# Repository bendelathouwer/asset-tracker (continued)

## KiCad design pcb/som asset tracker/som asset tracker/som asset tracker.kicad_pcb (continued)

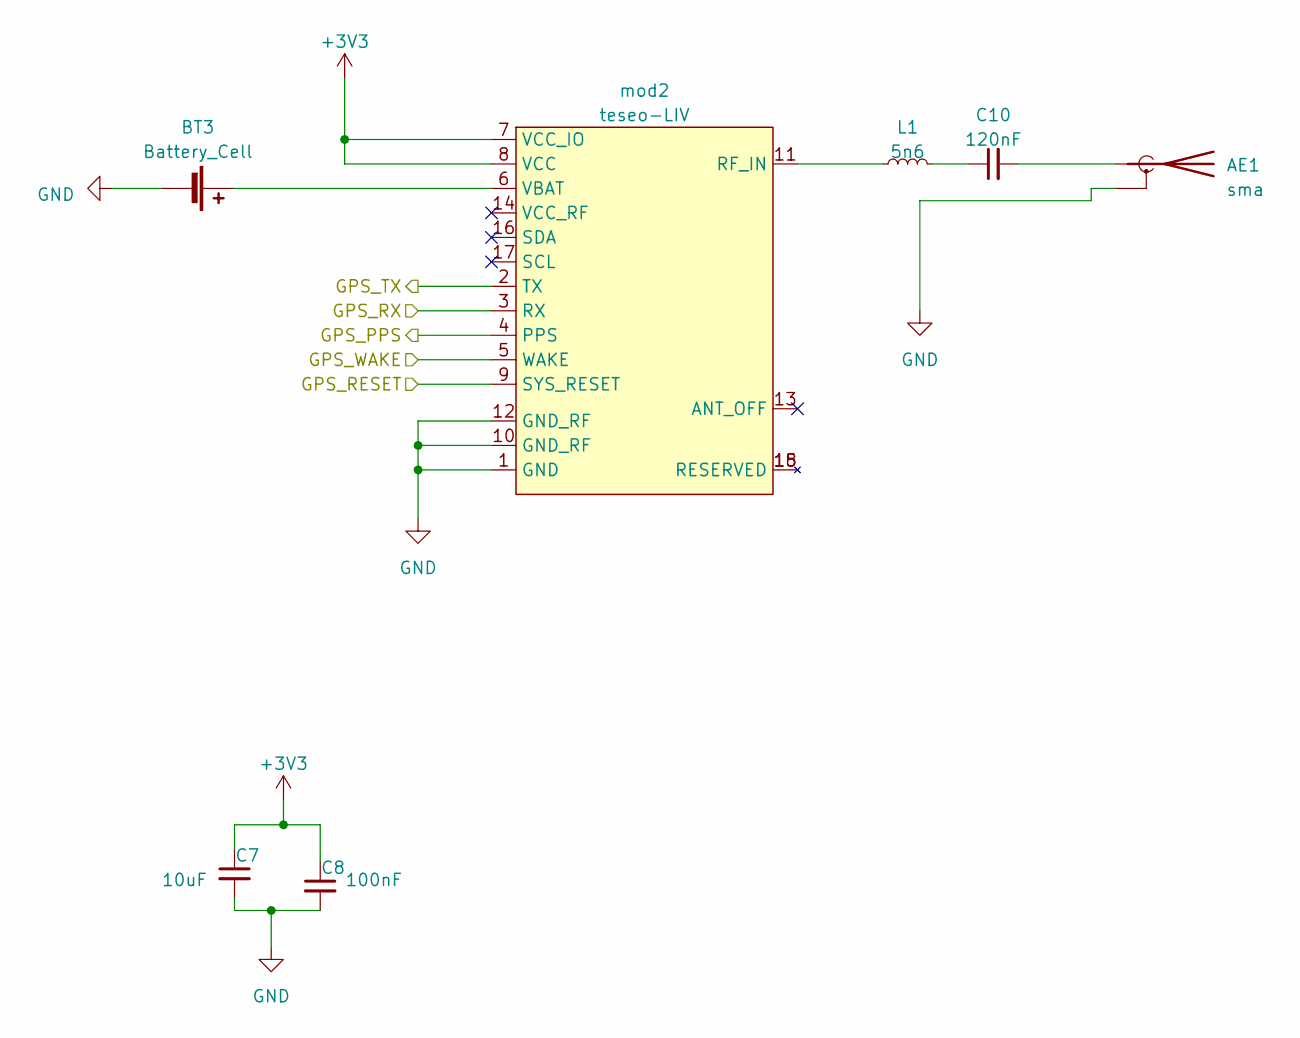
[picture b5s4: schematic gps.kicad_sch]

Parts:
AE1: sma; sma_right angeld
BT3: Battery_Cell; 3012TR
C7: 10uF; 0603
C8: 100nF; 0603
C10: 120nF; 0603
L1: 5n6; 0603
mod2: teseo-LIV; SON_STM_TESEO-LIV3R

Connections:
+3V3: C7.1, C8.1, mod2.7 (VCC_IO), mod2.8 (VCC); also elsewhere on the board
/PPS: mod2.4 (PPS); also elsewhere on the board
/RESET: mod2.9 (SYS_RESET); also elsewhere on the board
/RX: mod2.3 (RX); also elsewhere on the board
/TX: mod2.2 (TX); also elsewhere on the board
/WAKE: mod2.5 (WAKE); also elsewhere on the board
GND: AE1.2 (Shield), BT3.2 (-), C7.2, C8.2, mod2.1 (GND), mod2.10 (GND_RF), mod2.12 (GND_RF); also elsewhere on the board
unnamed: AE1.1 (A), C10.2
unnamed: BT3.1 (+), mod2.6 (VBAT)
unnamed: C10.1, L1.2
unnamed: L1.1, mod2.11 (RF_IN)

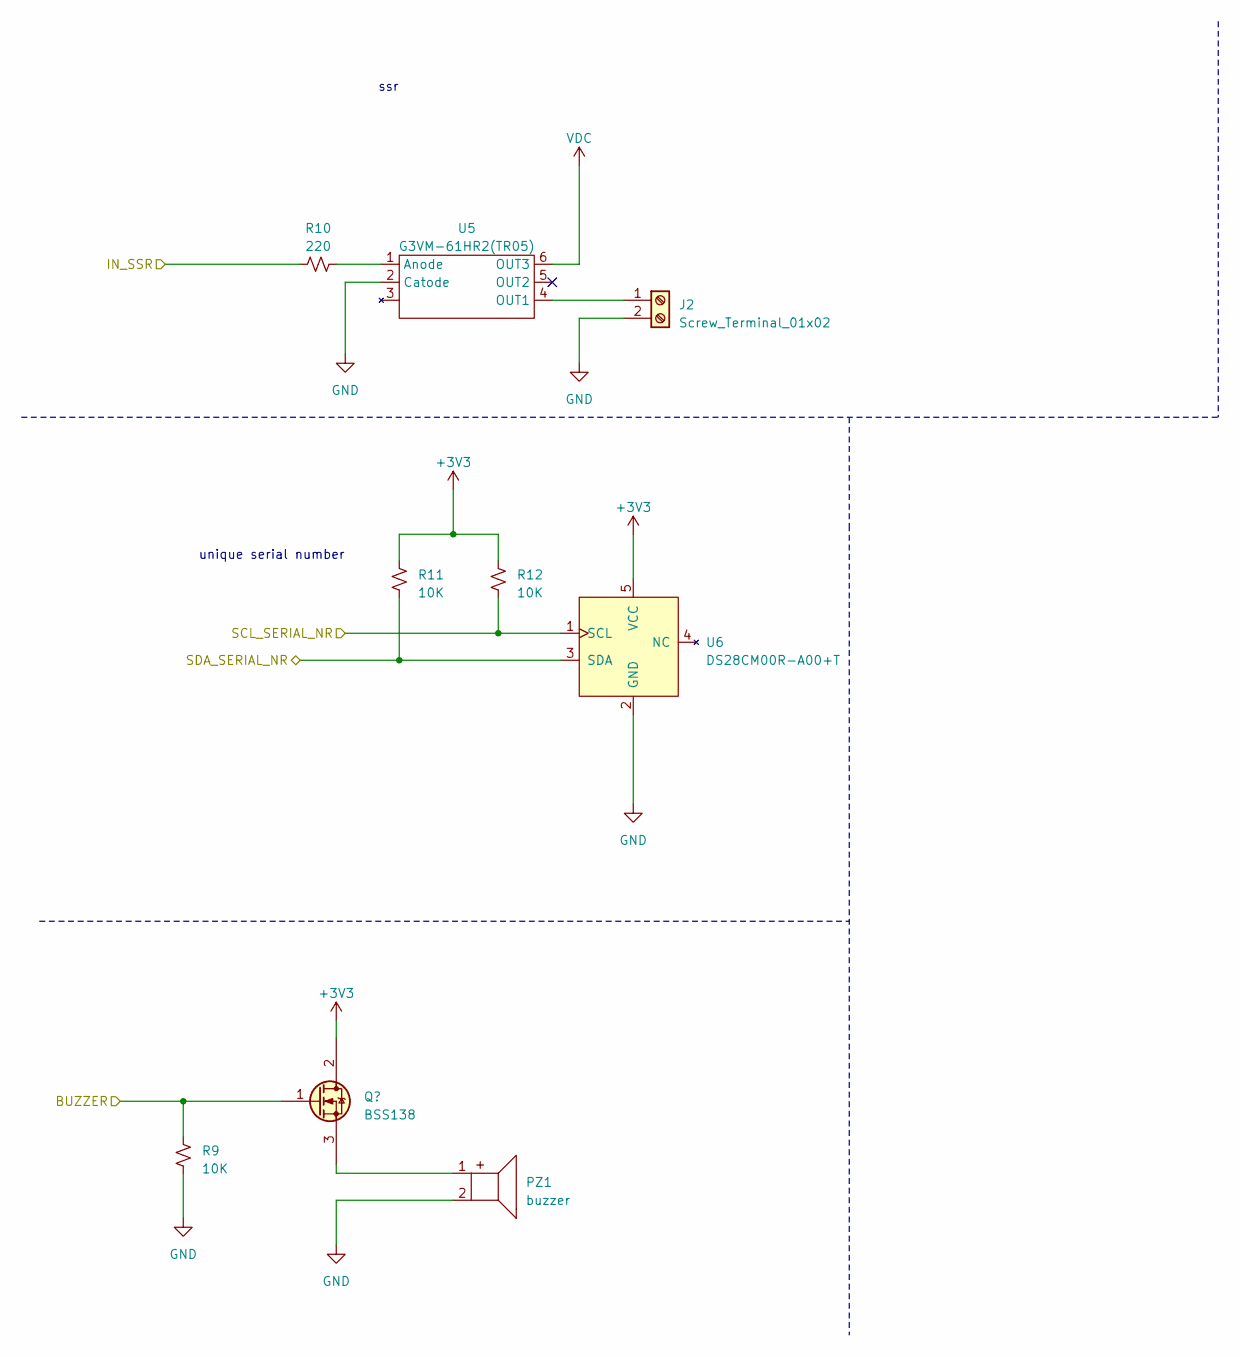
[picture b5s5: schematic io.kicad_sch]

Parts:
J2: Screw_Terminal_01x02; 2pin_screw
PZ1: buzzer; PROSIGNAL_ABI-017-RC
R9, R11, R12: 10K; 0603
R10: 220; 0603
U5: G3VM-61HR2(TR05); sop4 P=2.54
U6: DS28CM00R-A00+T; SOT-25

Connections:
+3V3: R11.1, R12.1, U6.5 (VCC); also elsewhere on the board
/BUZZER: R9.1; also elsewhere on the board
/SCL: R12.2, U6.1 (SCL); also elsewhere on the board
/SDA: R11.2, U6.3 (SDA); also elsewhere on the board
/SSR: R10.1; also elsewhere on the board
GND: J2.2, PZ1.2, R9.2, U5.2 (Catode), U6.2 (GND); also elsewhere on the board
unnamed: J2.1, U5.4 (OUT1)
unnamed 37: PZ1.1; also elsewhere on the board
unnamed: R10.2, U5.1 (Anode)
VDC: U5.6 (OUT3); also elsewhere on the board

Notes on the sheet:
unique serial number
ssr

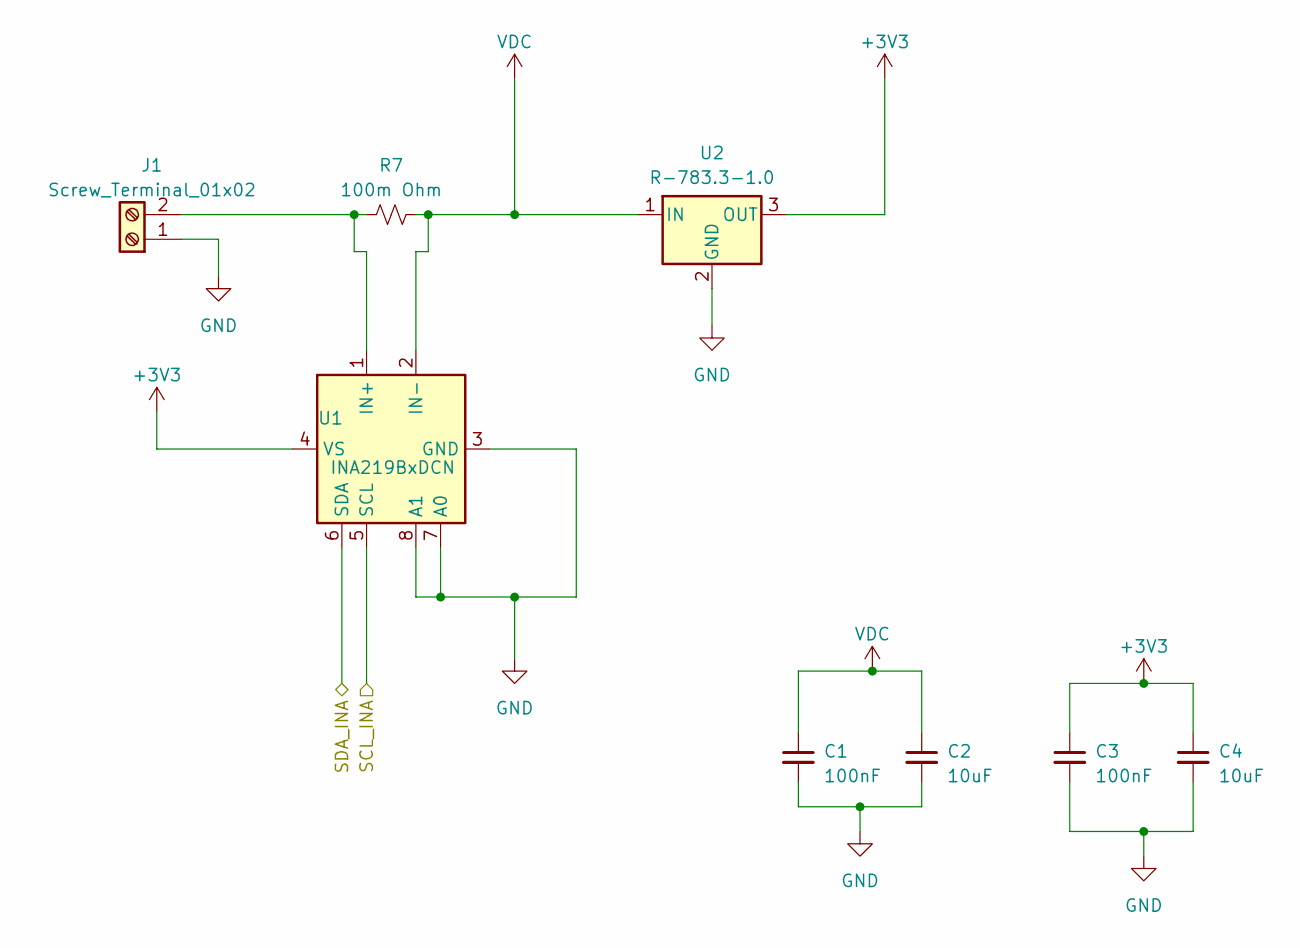
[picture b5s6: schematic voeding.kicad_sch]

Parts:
C1, C3: 100nF; 0603
C2, C4: 10uF; 0603
J1: Screw_Terminal_01x02; 2pin_screw
R7: 100m Ohm; R_2512_6332Metric_Pad1.40x3.35mm_HandSolder
U1: INA219BxDCN; SOIC127P599X175-8N
U2: R-783.3-1.0; recom psu

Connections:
+3V3: C3.1, C4.1, U1.4 (VS), U2.3 (OUT); also elsewhere on the board
/SCL: U1.5 (SCL); also elsewhere on the board
/SDA: U1.6 (SDA); also elsewhere on the board
GND: C1.2, C2.2, C3.2, C4.2, J1.1, U1.3 (GND), U1.7 (A0), U1.8 (A1), U2.2 (GND); also elsewhere on the board
unnamed: J1.2, R7.1, U1.1 (IN+)
VDC: C1.1, C2.1, R7.2, U1.2 (IN-), U2.1 (IN); also elsewhere on the board

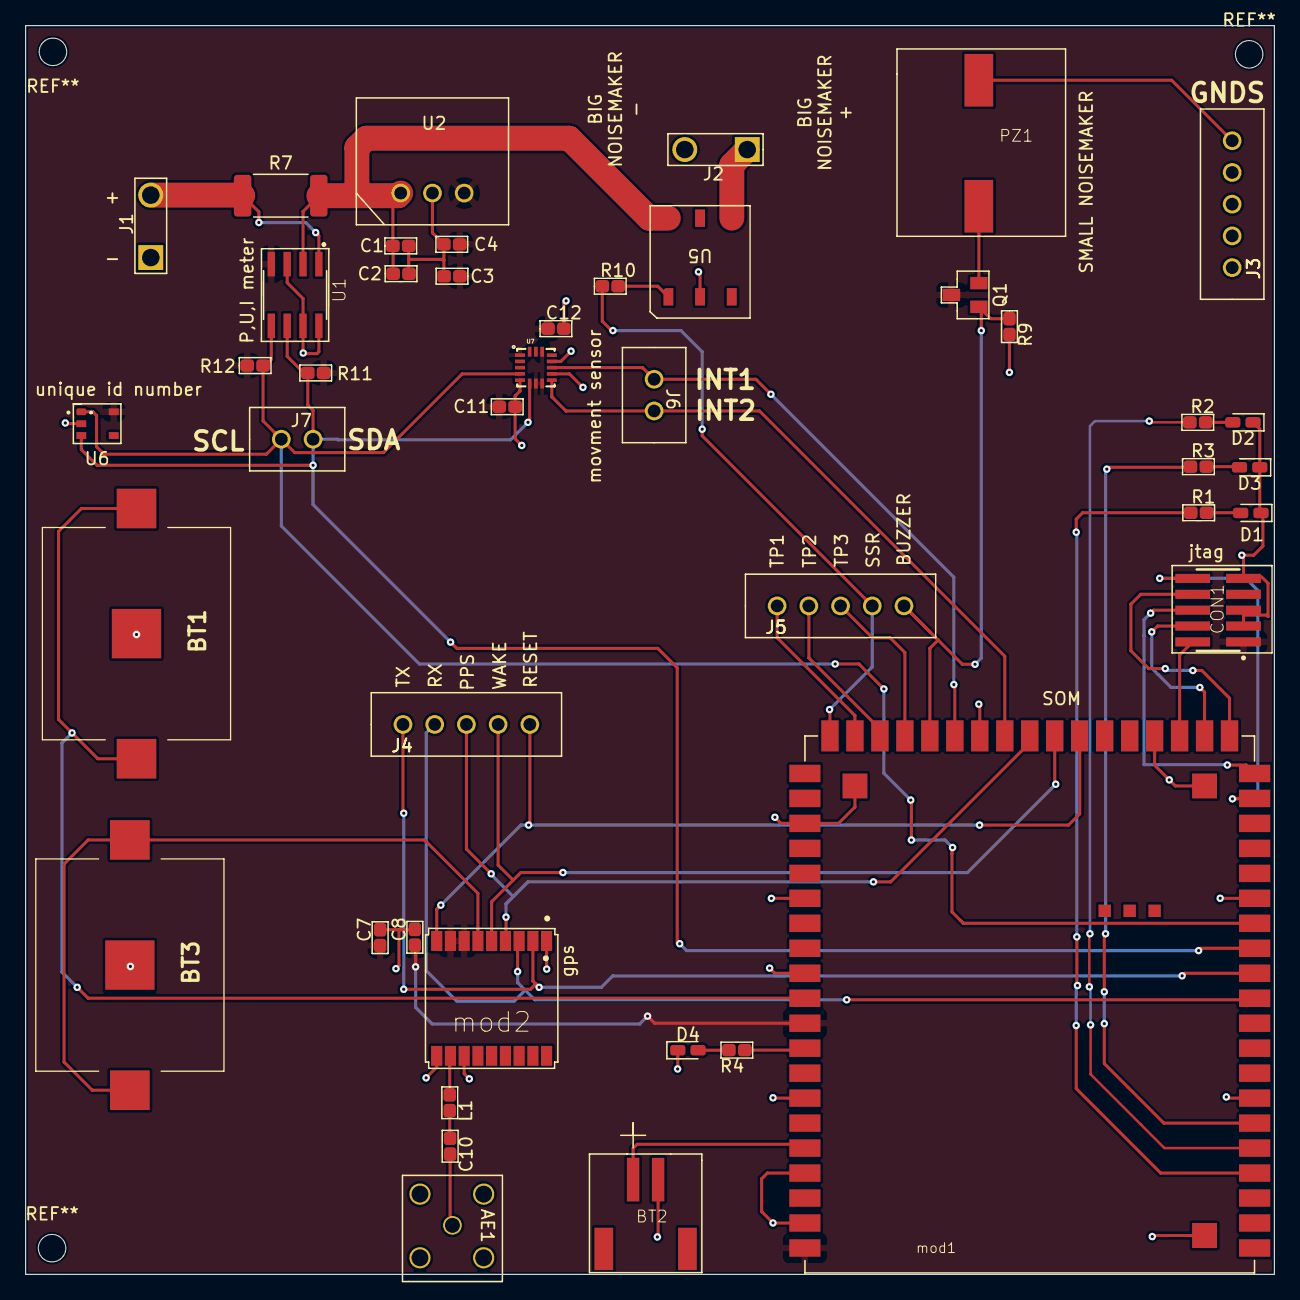
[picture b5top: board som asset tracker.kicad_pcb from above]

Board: 2 copper layers, 100.0 x 100.0 mm, 44 parts (0 on the bottom side), 40 nets.

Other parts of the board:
Q1: BBS3002; sot-23,

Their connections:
+3V3: Q1.3; also elsewhere on the board
/BUZZER: Q1.1; also elsewhere on the board
unnamed 37: Q1.2; also elsewhere on the board

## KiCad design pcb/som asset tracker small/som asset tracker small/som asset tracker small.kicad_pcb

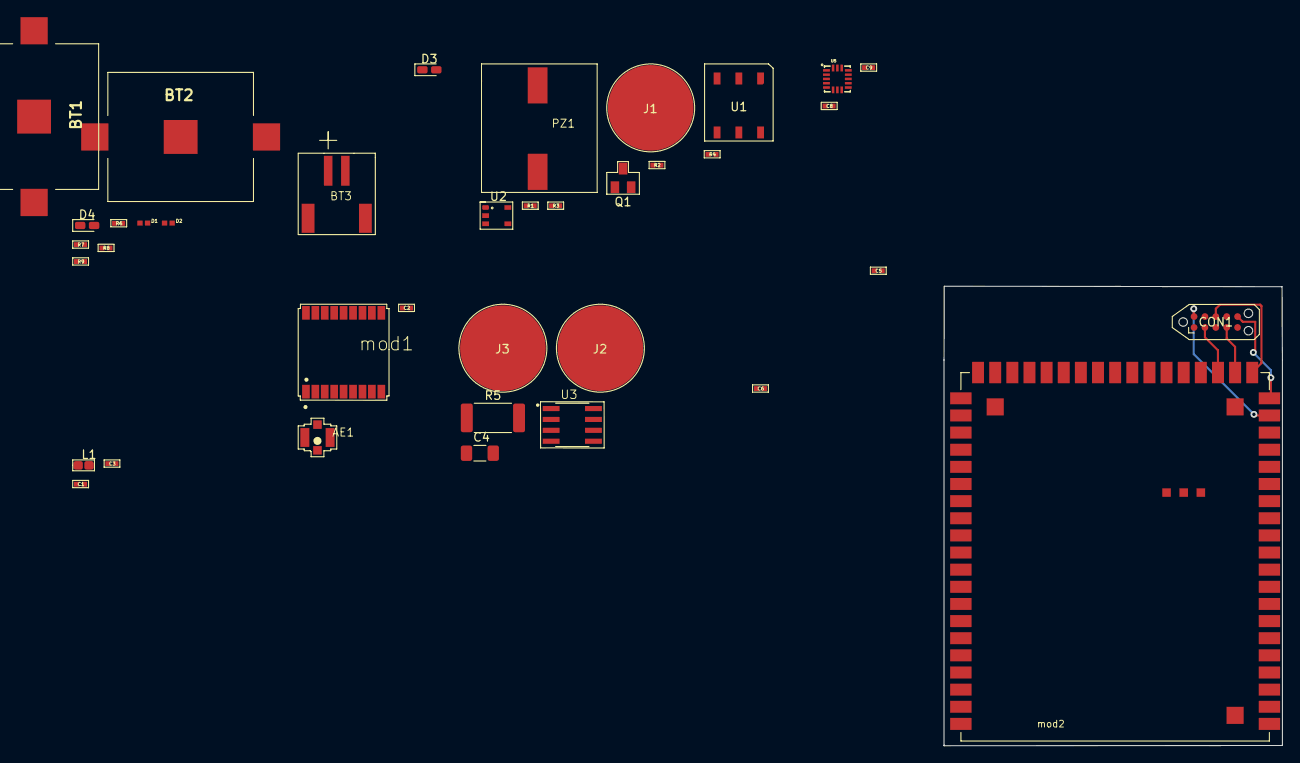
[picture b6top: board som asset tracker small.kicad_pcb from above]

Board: 2 copper layers, 39.5 x 53.6 mm, 38 parts (0 on the bottom side), 35 nets.

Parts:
AE1: sma; ufl connector
BT1: Battery_Cell; 3012TR
BT2: Battery; 3012TR
BT3: Battery; jst 2 pin
C1, C6, C8: 10uF; 0402
C2, C5, C9: 100nF; 0402
C3: 120nF; 0402
C4: 4.7uF; 1206
CON1: jtag; Tag-Connect_TC2050-IDC-NL_2x05_P1.27mm_Vertical
D1: RED; led 0402
D2: GREEN; led 0402
D3: BLUE; led0603
D4: pwr; led0603
J1, J2, J3: Screw_Terminal_01x01; smd screw terminal
L1: 5n6; 0603
PZ1: buzzer; PROSIGNAL_ABI-017-RC
Q1: BSS138; sot-23,
R1, R3, R4: 10K; 0402
R2, R6, R7, R8, R9: 220; 0402
R5: 100m Ohm; R_2512_6332Metric_Pad1.40x3.35mm_HandSolder
U1: G3VM-61HR2(TR05); sop4 P=2.54
U2: DS28CM00R-A00+T; SOT-25
U3: INA219BxDCN; SOIC127P599X175-8N
U5: LIS3DH; QFN-16_0.5MM
mod1: teseo-LIV; SON_STM_TESEO-LIV3R
mod2: particle_e0; E0

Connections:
+3V3: C1.1, C2.1, C5.1, C6.1, C8.1, C9.1, CON1.1 (VCC), Q1.2, R3.1, R4.1, U2.5 (VCC), U3.4 (VS), U5.1 (VDD_IO), U5.7 (SDO/SA0), U5.8 (CS), U5.14 (VDD), mod1.7 (VCC_IO), mod1.8 (VCC), mod2.1 (VIN), mod2.10 (VDDA)
/BUZZER: Q1.1, R1.1, mod2.25 (A1)
/INT1: U5.11 (INT1), mod2.26 (A0)
/INT2: U5.9 (INT2), mod2.28 (B5)
/PPS: mod1.4 (PPS), mod2.29 (B4)
/RESET: mod1.9 (SYS_RESET), mod2.31 (B2)
/RX: mod1.3 (RX), mod2.47 (C2)
/SCL: R4.2, U2.1 (SCL), U3.5 (SCL), U5.4 (SCL/SPC), mod2.44 (C5)
/SDA: R3.2, U2.3 (SDA), U3.6 (SDA), U5.6 (SDA/SDI/SDO), mod2.45 (C4)
/SOM/BLUE: R8.1, mod2.52 (BLUE)
/SOM/GREEN: R7.1, mod2.53 (GREEN)
/SOM/LIPO: BT3.1 (+), mod2.5 (LIPO)
/SOM/POWER: R9.1, mod2.9 (3V3)
/SOM/RED: R6.1, mod2.54 (RED)
/SOM/TCK: CON1.4 (SWDCLK/TCK), mod2.36 (D6)
/SOM/TDI: CON1.8 (NC/TDI), mod2.37 (D5)
/SOM/TDO: CON1.6 (SWO/TDO), mod2.38 (D4)
/SOM/TMS: CON1.2 (SWDIO/TMS), mod2.35 (D7)
/SOM/TRST: CON1.10 (tRST), mod2.39 (D3)
/SSR: R2.1, mod2.21 (A5)
/TX: mod1.2 (TX), mod2.46 (C3)
/WAKE: mod1.5 (WAKE), mod2.30 (B3)
GND: AE1.2 (Shield), BT1.2 (-), BT2.2 (-), BT3.2 (-), C1.2, C2.2, C4.2, C5.2, C6.2, C8.2, C9.2, CON1.3 (GND), CON1.5 (GND), CON1.9 (GND), D3.1 (K), D4.1 (K), J3.1, PZ1.2, R1.2, U1.2 (Catode), U2.2 (GND), U3.3 (GND), U3.7 (A0), U3.8 (A1), U5.5 (GND), U5.10 (GND), U5.12 (GND), mod1.1 (GND), mod1.10 (GND_RF), mod1.12 (GND_RF), mod2.2 (GND@2), mod2.4 (GND@4), mod2.7 (GND@7), mod2.12 (GND@12), mod2.15 (GND@15), mod2.18 (GND@18), mod2.27 (GND@27), mod2.34 (GND@34), mod2.43 (GND@43), mod2.51 (GND@51), mod2.58 (GND@PADS), mod2.59 (GND@PADS), mod2.60 (GND@PADS)
unnamed: AE1.1 (A), C3.2
unnamed: BT1.1 (+), mod1.6 (VBAT)
unnamed: BT2.1 (+), mod2.11 (VBAT)
unnamed: C3.1, L1.2
unnamed: C4.1, J2.1, R5.1, U3.1 (IN+)
unnamed: D3.2 (A), R8.2
unnamed: D4.2 (A), R9.2
unnamed: J1.1, U1.4 (OUT1)
unnamed: L1.1, mod1.11 (RF_IN)
unnamed: PZ1.1, Q1.3
unnamed: R2.2, U1.1 (Anode)
VDC: R5.2, U1.6 (OUT3), U3.2 (IN-)

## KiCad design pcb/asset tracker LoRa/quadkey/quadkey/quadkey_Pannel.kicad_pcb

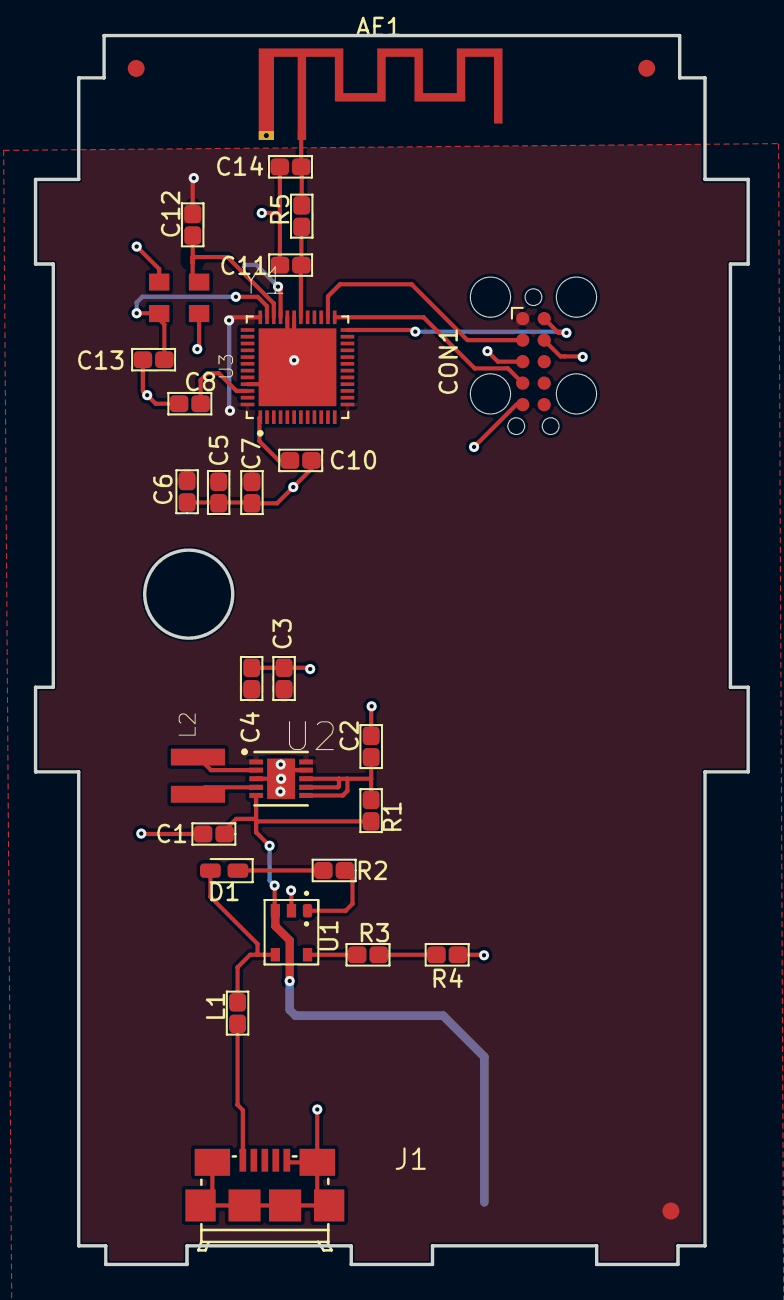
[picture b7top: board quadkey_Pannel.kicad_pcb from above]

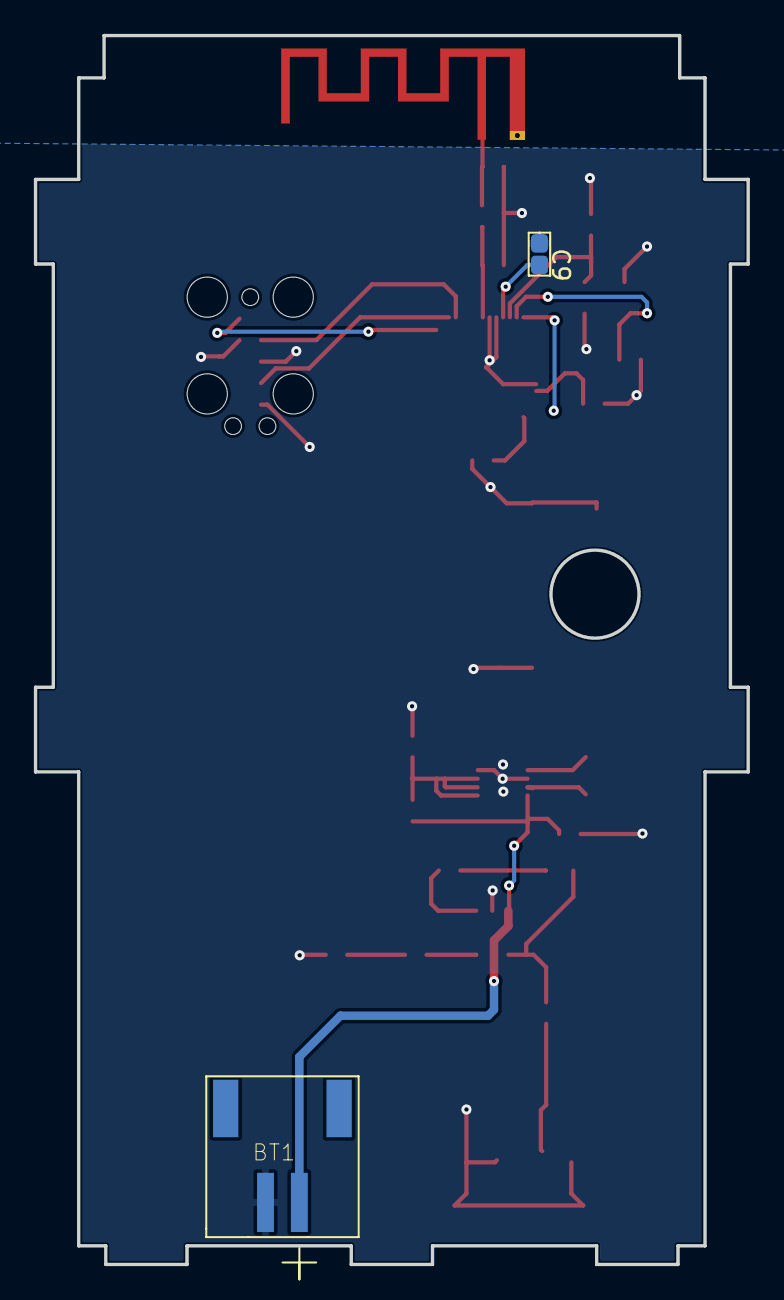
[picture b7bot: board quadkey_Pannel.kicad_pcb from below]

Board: 2 copper layers, 42.1 x 72.6 mm, 30 parts (2 on the bottom side), 22 nets.

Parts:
AE1: Antenna; Texas_SWRA117D_2.4GHz_Right
BT1: Battery; jst 2 pin
C1, C3, C4: 10uF; 0603
C2: 0.1uF; 0603
C5: 4.7uF; 0603
C6, C7, C10: 100nF; 0603
C8: 1uF; 0603
C9: 100pF; 0603
C11, C14: NM; 0603
C12, C13: 12pF; 0603
CON1: jtag; Tag-Connect_TC2050-IDC-FP_2x05_P1.27mm_Vertical
D1: LED; led0603
J1: USB_B_Mini; AMPHENOL_10118192-0001LF
L1: L; 0603RL
L2: 2.2uH; WURTH_744025001
R1: 100; 0603RL
R2: 1K; 0603RL
R3, R4: 1k; 0603RL
R5: 0; 0603RL
U1: MCP73831; SOT-25
U2: TPS63001; SON50P300X300X100-11N
U3: nRF52810-QFxx; nrf
Y1: 326MhZ; OSCCC320X250X90L80X100N

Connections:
+3V3: C3.1, C4.1, C5.2, C6.2, C7.2, CON1.1 (VCC), U2.1 (VOUT), U2.10 (FB), U3.13 (VDD), U3.36 (VDD), U3.48 (VDD)
/mcu/RST: CON1.10 (tRST), U3.24 (P0.21/~RESET)
/mcu/SWDCLK: CON1.4 (SWDCLK/TCK), U3.25 (SWDCLK)
/mcu/SWDIO: CON1.2 (SWDIO/TMS), U3.26 (SWDIO)
GND: BT1.2 (-), C1.2, C2.2, C3.2, C4.2, C5.1, C6.1, C7.1, C8.1, C9.1, C10.1, C11.2, C12.2, C13.2, C14.2, CON1.3 (GND), CON1.5 (GND), CON1.9 (GND), J1.5 (GND), J1.6 (Shield), R4.1, U1.2 (VSS), U2.3 (PGND), U2.9 (GND), U2.11 (PGND), U3.31 (VSS), U3.32 (DEC2), U3.45 (VSS), U3.49 (VSS), Y1.2, Y1.4
unnamed: AE1.1 (A), C14.1, R5.2
unnamed: C2.1, R1.1, U2.6 (EN), U2.7 (PS/SYNC), U2.8 (VINA)
unnamed: C8.2, U3.46 (DEC4)
unnamed: C9.2, U3.33 (DEC3)
unnamed: C10.2, U3.1 (DEC1)
unnamed: C11.1, R5.1, U3.30 (ANT)
unnamed: C12.1, U3.34 (XC1), Y1.3
unnamed: C13.1, U3.35 (XC2), Y1.1
unnamed: D1.1 (K), R2.2
unnamed: J1.1 (VBUS), L1.1
unnamed: L2.1, U2.4 (L1)
unnamed: L2.2, U2.2 (L2)
unnamed: R2.1, U1.1 (STAT)
unnamed: R3.1, U1.5 (Prog)
unnamed: R3.2, R4.2
VBAT: BT1.1 (+), C1.1, R1.2, U1.3 (VBAT), U2.5 (VIN)
VBUS: D1.2 (A), L1.2, U1.4 (VDD)

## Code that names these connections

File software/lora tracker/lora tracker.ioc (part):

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PC15-OSC32_OUT.Mode=LSE-External-Oscillator
PA6.Mode=Full_Duplex_Master
PA7.Mode=Full_Duplex_Master
PA10.Mode=Multiprocessor_communication
Mcu.UserName=STM32L052K6Tx
PA0.GPIO_Label=buzzer
PA12.GPIOParameters=GPIO_Label
PA11.GPIOParameters=GPIO_Label
PA11.GPIO_Label=GPS_WAKE
PC14-OSC32_IN.Signal=RCC_OSC32_IN
PA12.GPIO_Label=GPS_PPS
PB5.GPIOParameters=GPIO_Label
PA3.Mode=Multiprocessor_communication
PA13.Signal=SYS_SWDIO
PA9.Mode=Multiprocessor_communication
PA12.Signal=GPIO_Input
PA4.Mode=NSS_Signal_Hard_Output
PA9.Signal=USART1_TX
PB6.Signal=I2C1_SCL
PB6.Mode=I2C
PC15-OSC32_OUT.Signal=RCC_OSC32_OUT
PA1.Signal=GPIO_Output
PA5.Signal=SPI1_SCK
PB0.Mode=IN8
board=custom
PA1.GPIOParameters=GPIO_Label
PC14-OSC32_IN.Mode=LSE-External-Oscillator
PA14.Mode=Serial_Wire
PA1.GPIO_Label=SSR
PB3.GPIOParameters=GPIO_Label
PB7.Signal=I2C1_SDA
PA8.Signal=GPIO_Output
PA13.Mode=Serial_Wire
Mcu.Name=STM32L052K(6-8)Tx
PA2.Signal=USART2_TX
PA0.Signal=GPIO_Output
PB3.Signal=GPIO_Output
PA4.Signal=SPI1_NSS
RCC.SYSCLKFreq_VALUE=2097000
Mcu.Package=LQFP32
PB5.Signal=GPIO_Input
PA6.Signal=SPI1_MISO
PB7.Mode=I2C
PA11.Signal=GPIO_Output
PA10.Signal=USART1_RX
PA14.Signal=SYS_SWCLK
PA0.GPIOParameters=GPIO_Label
PB5.GPIO_Label=LIS_INT1
PA2.Mode=Multiprocessor_communication
PB0.Signal=ADC_IN8
PB4.Signal=GPIO_Input
PA3.Signal=USART2_RX
PA7.Signal=SPI1_MOSI
PA5.Mode=Full_Duplex_Master
PB3.GPIO_Label=LORA_RESET

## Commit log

2021-04-21 start
    opzoek werken gedaan naar chips etc
2021-04-21 kicad project
    kicad project in gang gestoken
2021-04-28 som board
    som test board done
2021-04-28 clasificatie
    op naar een betere clasificatie
2021-05-17 key
    pcb for the key
2021-05-17 quadkey
    quadkey print klaar
2021-05-18 34t
    34t
2021-05-19 pcb kastje
    pcb in kastje getekend
2021-05-21 lora tracker
    lora tracker afgemaakt
2021-05-21 klaar
    pcb klaar
2021-05-31 klaar
    print hertekend naar stm32L5
2021-05-31 verandering
    iets veranderd
2021-05-31 module firmware
    module firmware toegevoegd
2021-05-31 code
    aan de code gestard
2021-06-04 code
    code
2021-06-04 schema
    schema hergetekend
2021-06-07 remake
    remake 2 van de print
2021-06-11 versie2
    aan versie 2 begonnen met tekenen en code beginnen schrijven voor quadkey
2021-06-11 quadkey
    software voor de quadkey "afgeschreven"
2021-06-11 code
    code lora_tracker esp begonnen met schrijven
2021-06-22 altium pcb
    start altium pcb
2021-06-25 altium pcb v3
    altium pcb v3
2021-06-25 current sensor +DCDC convertor
    current sensor bijna klaar en DCDC convertor kan nu >48V aan
2021-06-25 altium
    current sensor
2021-06-28 versie3
    versie 3 van pcb bijna getekend buiten de microcontroller
2021-06-29 loratracker V3
    schema's voor de verbeterde loratracker bijna af
2021-07-04 Key Tranceiver
2021-07-04 Update EC_Key.ino
    - EMPTY_UUID is BLEUUID("00000000-0000-0000-0000-00000000000")
2021-07-05 schema mcu
    schema mcu bijna klaar
2021-07-05 schema
    schem bijna af versie 2
2021-07-05 schema's
    schema's bijna af
2021-07-05 jst
    jst datasheet toegevoegd
2021-07-06 ferg
    werg
2021-07-07 schema
    schema versie 2 afgetekend
2021-07-13 schema's
    Schema's afgetekend
2021-07-14 software
    software gestart
2021-07-15 software
    Software begonnen
2021-07-20 quadkey
    quadkey begonnen
2021-07-20 quadkey
    quadkey schema opgemaakt
2021-07-26 schema klaar
    schema dc-dc klaar
2021-07-27 datasheet+footprints
    assigning footprints and added datasheet for the dual diode
2021-07-27 voedingsprint kicad
2021-07-27 voedings print voor v1
    voedingsprint getekend voor tracker V1
2021-07-29 dwf
    dsf
2021-07-29 werg
    werg
2021-07-29 ref design
    esp32prog refrence design
2021-07-29 datasheet
    datasheet toegevoegd
2021-07-30 wef
    wef
2021-08-02 harnass
    harnassen
2021-08-03 voedings PCB
    Voedings pcb schema afgetekend
2021-08-04 schema voedingswitcher af
    voeding switcher voor v1 afgetekend
2021-08-05 zdsxvc
    zxcv
2021-08-05 schema
    schema aangevuld
2021-08-08 fb
    dfb
2021-08-09 voedings switcher schematic
    voedings switcher schema afgetekend
2021-08-09 sfv
    fv
2021-08-09 erger
    erg
2021-08-10 opkuis
    repository opgekuist
2021-08-12 qwedf
    qedf
2021-08-12 Bom
    Bom toegevoegd
2021-08-16 grr
    g
2021-08-16 key qi
    key qi
2021-08-16 keyqi
    key qi toegevoegd
2021-08-17 ec qikey
    ec qikey bijna afgewerkt.
2021-08-19 eadf
    sdfv
2021-08-19 refsd
    fsdf
2021-08-30 bla
    blabla
2021-09-01 sdf
    fsgv
2021-09-06 wrg
    erg
2021-09-06 V3
    V3 pcb
2021-09-07 dc
    dsc
2021-09-08 versie 3
    verscie 3 afgetekend
2021-09-08 v3
    v3 bijna af
2021-09-14 key
    key schema afgetekend
2021-09-15 firmware
    aan de firmware beginnen schrijven
2021-09-17 software
    I2C libary test
2021-09-17 software io
    software io gestart
2021-09-17 gps
    gps software begonnen
2021-09-22 documentatie
    Documentatie toegevoegd
2021-09-24 qsfrr
    wef
2021-09-27 code
    Code en libary beginnen schrijven
2021-09-27 CODE
    code verder geschreven
2021-09-28 pcb
    altium pcb
2022-04-30 qewf
    wetr
2022-05-27 fgnhb
    fgdh
